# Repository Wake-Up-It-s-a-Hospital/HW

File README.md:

# Hardware

##### 환자 추종 스마트 링거 폴대의 PCB 및 HW 설계를 담당하는 레포지토리입니다.

_구동부, 손잡이부, 스마트 기능부에 해당하는 PCB 설계 및 회로도와 각각의 부분에 해당하는 HW 설계 및 3D modeling 등을 설계하였습니다._

본 레포지토리는 **2025년 한국공학대학교 종합설계 (캡스톤디자인) 프로젝트**와 **한이음 프로젝트**의 지원을 받아 개발되고 있습니다.

---
### ✅ 현재까지 완성한 Hardware

#### :diamond_shape_with_a_dot_inside: 1. 구동부 부분의 프로파일 및 아크릴 설계 도면

- 정육각형 구동부 상자의 모서리 역할인 프로파일 도면

- 정육각형 구동부 상자의 면 역할인 아크릴 설계 도면
  - 각종 PCB, 소자, 배터리, 폴대 장착에 맞추어 타공

#### :diamond_shape_with_a_dot_inside: 2.  PCB 설계 도면

- 구동부, 손잡이부, 스마트 기능부
 
- 각각 KiCAD를 사용해서 제작
  - 별칭
    - 구동부 : 1층
    - 손잡이부 : 2층
    - 카메라부 : 3층
    - 스마트 기능부 : 4층
    - 스마트 웨어러블 기기 : 시계부
-  2층* 을 제외한 모든 PCB 는 KiCAD 버전 9.0으로 작성됨.
  
-  2층은 KiCAD 8.0 버전으로 작성됨.

- connector는 모두 molex 5264(수), 5267(암)을 사용함.
- 전원 connector는 5557(수), 5566(암)을 사용함.

#### :diamond_shape_with_a_dot_inside: 3. 3D Modeling
- STM32로부터 수신한 데이터 패킷(lost 상황, 자동/수동 모드)을 AWS 서버로 전송

- NodeRed연동된 스마트 웨어러블 기기와 실시간으로 통신하여 경고 알림 제공

#### :diamond_shape_with_a_dot_inside: 4. 자동 / 수동 모드 전환 기능
- 링거 폴대 하부의 버튼 입력을 통해 자동 ↔ 수동 모드 전환 가능

---
## Data Flow

```mermaid
sequenceDiagram
    participant ESP32_LEFT as ESP32 (HUSKY_LEFT)
    participant STM32
    participant ESP32_RIGHT as ESP32 (HUSKY_RIGHT)

    ESP32_LEFT->>STM32: θ (조향각), currentMode (자동/수동)
    STM32->>ESP32_RIGHT: SoC (State of Charge)
    STM32->>ESP32_LEFT: lost 상태, SoC (State of Charge)

```

## 📁 주요 버전 디렉토리 구조

```
Patient-Recognition/
├── latest version/
|  ├──HUSKY_LEFT_AWS_V1_0       #ESP32 LEFT 
|  ├──HUSKY_RIGHT_WIFI_V1_0     #ESP32 RIGHT
├── test version/
|  ├──remote_control0           #이전 버전 원격 조정
|  ├──remote_control1           #최신 버전 원격 조정
|  ├──remote_master             #STM32 측 구동부
├── previous version/
|  ├──HUSKY_SERVO_V2_0          # 이전 버전 (서보모터 사용 허스키 1개)
|  ├──HUSKY_SErVO_V3_0
```

---

## 설치 및 실행 방법

### 1. HUSKYLENS 펌웨어
1) Arduino IDE 설치
2) HUSKYLENS header file 설치
[HUSKYLENS 공식 문서](https://wiki.dfrobot.com/HUSKYLENS_V1.0_SKU_SEN0305_SEN0336#target_6)

**헤더 파일 오류시**

HuskyLensProtocolCore.C에서

    uint8_t* husky_lens_protocol_write_begin()
    {
        return &send_buffer;
    }

에서 return 값 변경(ESP32와의 호환성 문제)

    uint8_t* husky_lens_protocol_write_begin()
    {
        return send_buffer;
    }

3) `latest version` 폴더 열어 LEFT, RIGHT 선택
4) 해당 코드에 맞는 좌우 HUSKYLENS 연결
5) 기본 HW 연결 세팅 확인 및 펌웨어 업로드

> :electric_plug: 기본 HW 세팅 회로도

### 2. HUSKYLENS HW 장착
 1) HW Repository Camera Cover file 열기
 2) HW Repository Camera Clamp file 열기
 3) HW Repository 2ndfloor_pole_bracket 열기
 4) HW Repository 2ndfloor_pole_bracket_RIGHT 열기
 5) 3D 프린터로 해당 Cover 인쇄 (2EA)
 6) 3D 프린터로 해당 Clamp 인쇄 (1EA)
 7) 3D 프린터로 해당 bracket, brackeet_RIGHT 인쇄 (각 1EA)
 8) 좌우 구분하여 LEFT, RIGHT HUSKYLENS 장착

 ### 3. STM32와의 통신선 연결 (UART)
 1) STM32와의 UART (TX, RX) 연결
 2) STM32와는 통신선 교차 연결

> :electric_plug: 기본 통신선 세팅 회로도

## :iphone: 주요 기능

### 환자 인식
 - 허스키렌즈를 통한 환자 인식
 - ID 별 인식 구별을 통한 다른 환자의 환자복 인식 방지 기능
 - 허스키렌즈 2개를 통한 조향각 매핑

 ### 데이터 통신
 - STM32와의 주요 factor 통신 (UART)
 - 스마트 웨어러블 기기와의 통신 (AWS NodeRed)

 ## :pushpin:  TODO (예정 기능)

 - [x] pull-up 저항 PCB 업데이트
 - [x] beacon 을 활용한 폴대 사용자의 위치 추정 기술
 - [x] 왼쪽 허스키 교체 (부품)
 - [x] ???

---
 ## 🤝 기여하기

1. 이 저장소를 포크합니다
2. 새로운 기능 브랜치를 생성합니다 (`git checkout -b feature/AmazingFeature`)
3. 변경사항을 커밋합니다 (`git commit -m 'Add some AmazingFeature'`)
4. 브랜치에 푸시합니다 (`git push origin feature/AmazingFeature`)
5. Pull Request를 생성합니다

---

## 📝 라이선스

이 프로젝트는 [MIT License](LICENSE)를 따릅니다. 자유롭게 사용, 수정, 배포하셔도 좋습니다.

---

## 📬 연락처

- ✉️ dy061932@tukorea.ac.kr  (학교)
- ✉️ dy353020@naver.com      (개인)

---

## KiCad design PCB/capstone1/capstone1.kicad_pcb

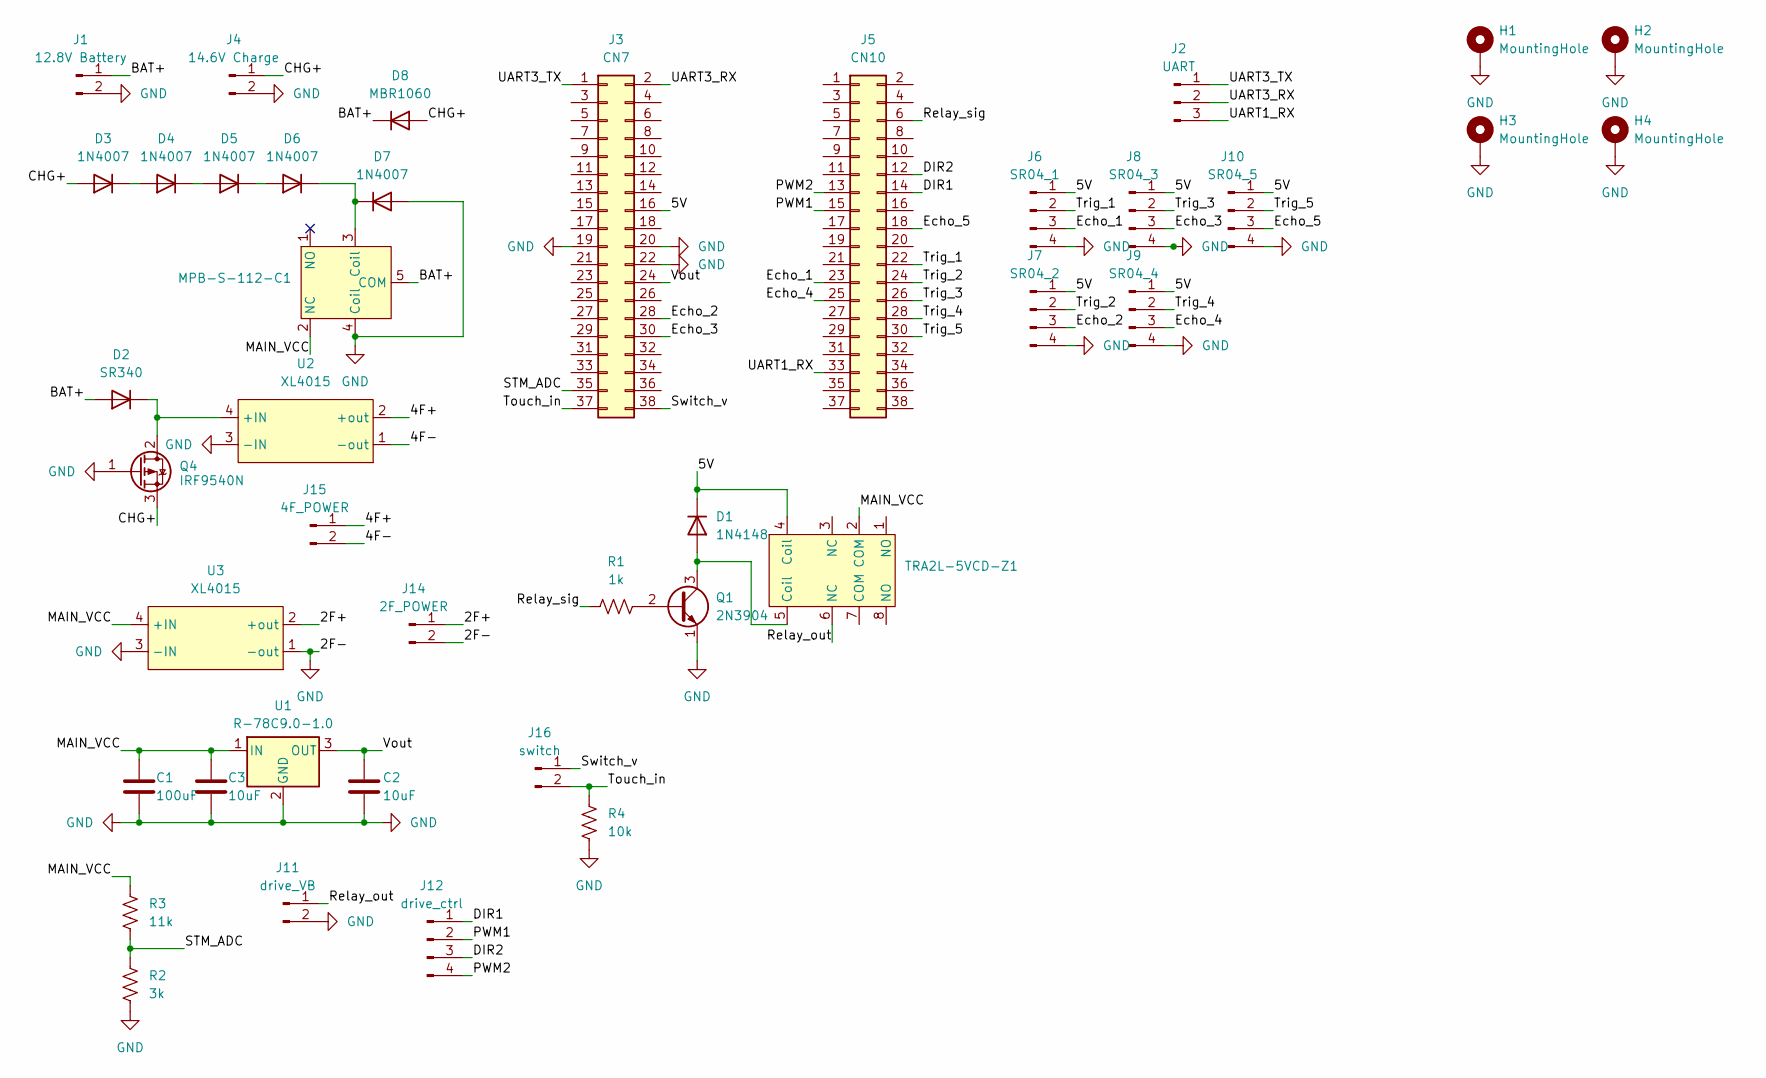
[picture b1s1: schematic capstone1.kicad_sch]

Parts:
C1: 100uF; CP_Elec_6.3x5.3
C2, C3: 10uF; C_1206_3216Metric
D1: 1N4148; D_DO-35_SOD27_P7.62mm_Horizontal
D2: SR340; D_DO-41_SOD81_P10.16mm_Horizontal
D3, D4, D5, D6, D7: 1N4007; D_DO-41_SOD81_P10.16mm_Horizontal
D8: MBR1060; TO-220-2_Vertical
H1, H2, H3, H4: MountingHole; MountingHole_2.5mm_Pad
J1: 12.8V Battery; Molex_Mini-Fit_Jr_5566-02A_2x01_P4.20mm_Vertical
J2: UART; Molex_SPOX_5267-03A_1x03_P2.50mm_Vertical
J3: CN7; PinSocket_2x19_P2.54mm_Vertical
J4: 14.6V Charge; Molex_Mini-Fit_Jr_5566-02A_2x01_P4.20mm_Vertical
J5: CN10; PinSocket_2x19_P2.54mm_Vertical
J6: SR04_1; Molex_SPOX_5267-04A_1x04_P2.50mm_Vertical
J7: SR04_2; Molex_SPOX_5267-04A_1x04_P2.50mm_Vertical
J8: SR04_3; Molex_SPOX_5267-04A_1x04_P2.50mm_Vertical
J9: SR04_4; Molex_SPOX_5267-04A_1x04_P2.50mm_Vertical
J10: SR04_5; Molex_SPOX_5267-04A_1x04_P2.50mm_Vertical
J11: drive_VB; Molex_Mini-Fit_Jr_5566-02A_2x01_P4.20mm_Vertical
J12: drive_ctrl; Molex_SPOX_5267-04A_1x04_P2.50mm_Vertical
J14: 2F_POWER; Molex_Mini-Fit_Jr_5566-02A_2x01_P4.20mm_Vertical
J15: 4F_POWER; Molex_Mini-Fit_Jr_5566-02A_2x01_P4.20mm_Vertical
J16: switch; Molex_Mini-Fit_Jr_5566-02A_2x01_P4.20mm_Vertical
MPB-S-112-C1: MPB-S-112-C
Q1: 2N3904; TO-92_Inline
Q4: IRF9540N; TO-220-3_Vertical
R1: 1k; R_1206_3216Metric
R2: 3k; R_1206_3216Metric
R3: 11k; R_1206_3216Metric
R4: 10k; R_1206_3216Metric
TRA2L-5VCD-Z1: TRA2L-5VCD-Z
U1: R-78C9.0-1.0; Converter_DCDC_RECOM_R-78E-0.5_THT
U2, U3: XL4015

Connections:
/2F+: J14.1, U3.2 (+out)
/4F+: J15.1, U2.2 (+out)
/4F-: J15.2, U2.1 (-out)
/5V: D1.1 (K), J3.16, J6.1, J7.1, J8.1, J9.1, J10.1, TRA2L-5VCD-Z1.4 (Coil)
/BAT+: D2.2 (A), D8.1 (K), J1.1, MPB-S-112-C1.5 (COM)
/CHG+: D3.2 (A), D8.2 (A), J4.1, Q4.3 (S)
/DIR1: J5.14, J12.1
/DIR2: J5.12, J12.3
/Echo_1: J5.23, J6.3
/Echo_2: J3.28, J7.3
/Echo_3: J3.30, J8.3
/Echo_4: J5.25, J9.3
/Echo_5: J5.18, J10.3
/MAIN_VCC: C1.1, C3.1, MPB-S-112-C1.2 (NC), R3.1, TRA2L-5VCD-Z1.2 (COM), U1.1 (IN), U3.4 (+IN)
/PWM1: J5.15, J12.2
/PWM2: J5.13, J12.4
/Relay_out: J11.1, TRA2L-5VCD-Z1.6 (NC)
/Relay_sig: J5.6, R1.1
/STM_ADC: J3.35, R2.1, R3.2
/Switch_v: J3.38, J16.1
/Touch_in: J3.37, J16.2, R4.1
/Trig_1: J5.22, J6.2
/Trig_2: J5.24, J7.2
/Trig_3: J5.26, J8.2
/Trig_4: J5.28, J9.2
/Trig_5: J5.30, J10.2
/UART1_RX: J2.3, J5.33
/UART3_RX: J2.2, J3.2
/UART3_TX: J2.1, J3.1
/Vout: C2.1, J3.24, U1.3 (OUT)
GND: C1.2, C2.2, C3.2, D7.2 (A), H1.1, H2.1, H3.1, H4.1, J1.2, J3.19, J3.20, J3.22, J4.2, J6.4, J7.4, J8.4, J9.4, J10.4, J11.2, J14.2, MPB-S-112-C1.4 (Coil), Q1.1 (E), Q4.1 (G), R2.2, R4.2, U1.2 (GND), U2.3 (-IN), U3.1 (-out), U3.3 (-IN)
unnamed: D1.2 (A), Q1.3 (C), TRA2L-5VCD-Z1.5 (Coil)
unnamed: D2.1 (K), Q4.2 (D), U2.4 (+IN)
unnamed: D3.1 (K), D4.2 (A)
unnamed: D4.1 (K), D5.2 (A)
unnamed: D5.1 (K), D6.2 (A)
unnamed: D6.1 (K), D7.1 (K), MPB-S-112-C1.3 (Coil)
unnamed: Q1.2 (B), R1.2

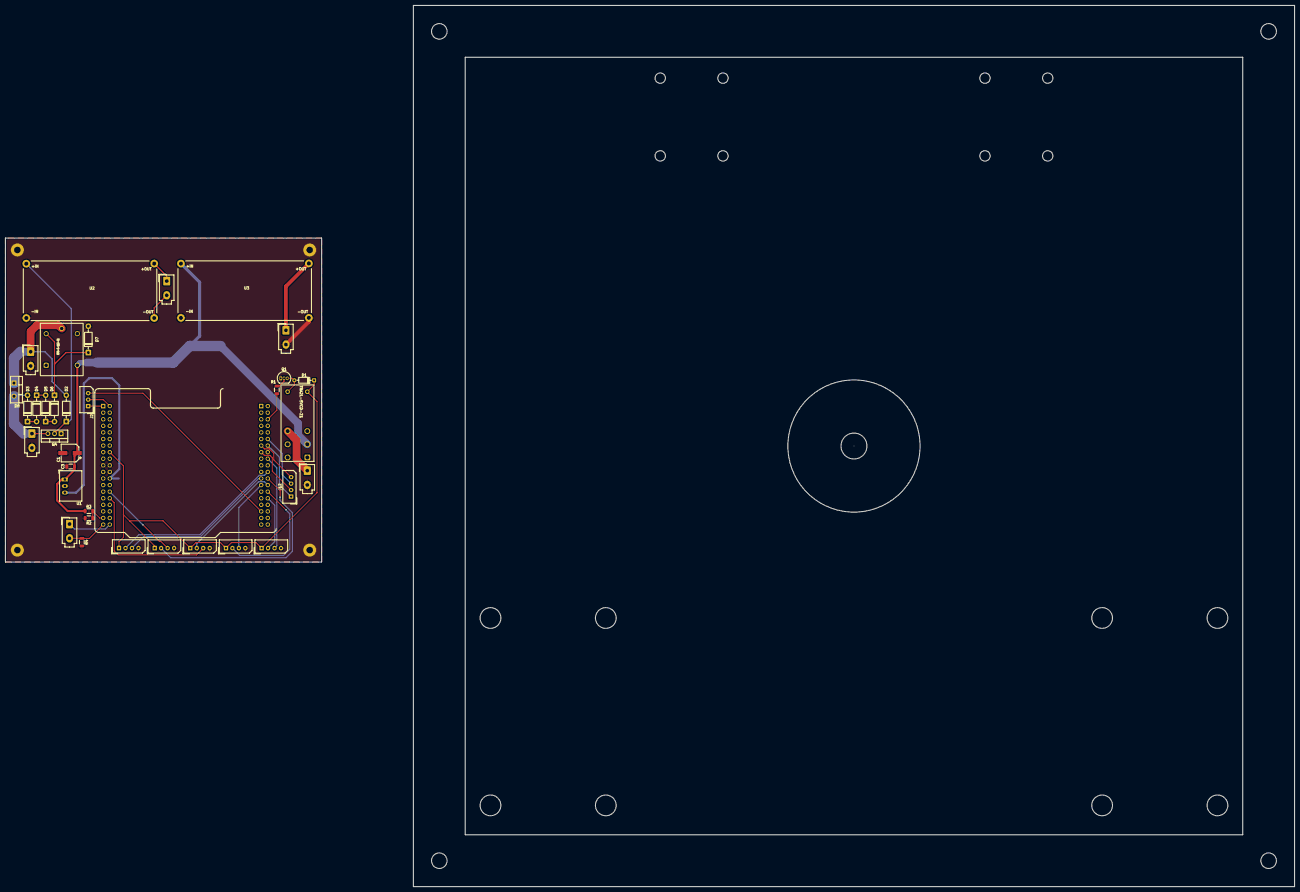
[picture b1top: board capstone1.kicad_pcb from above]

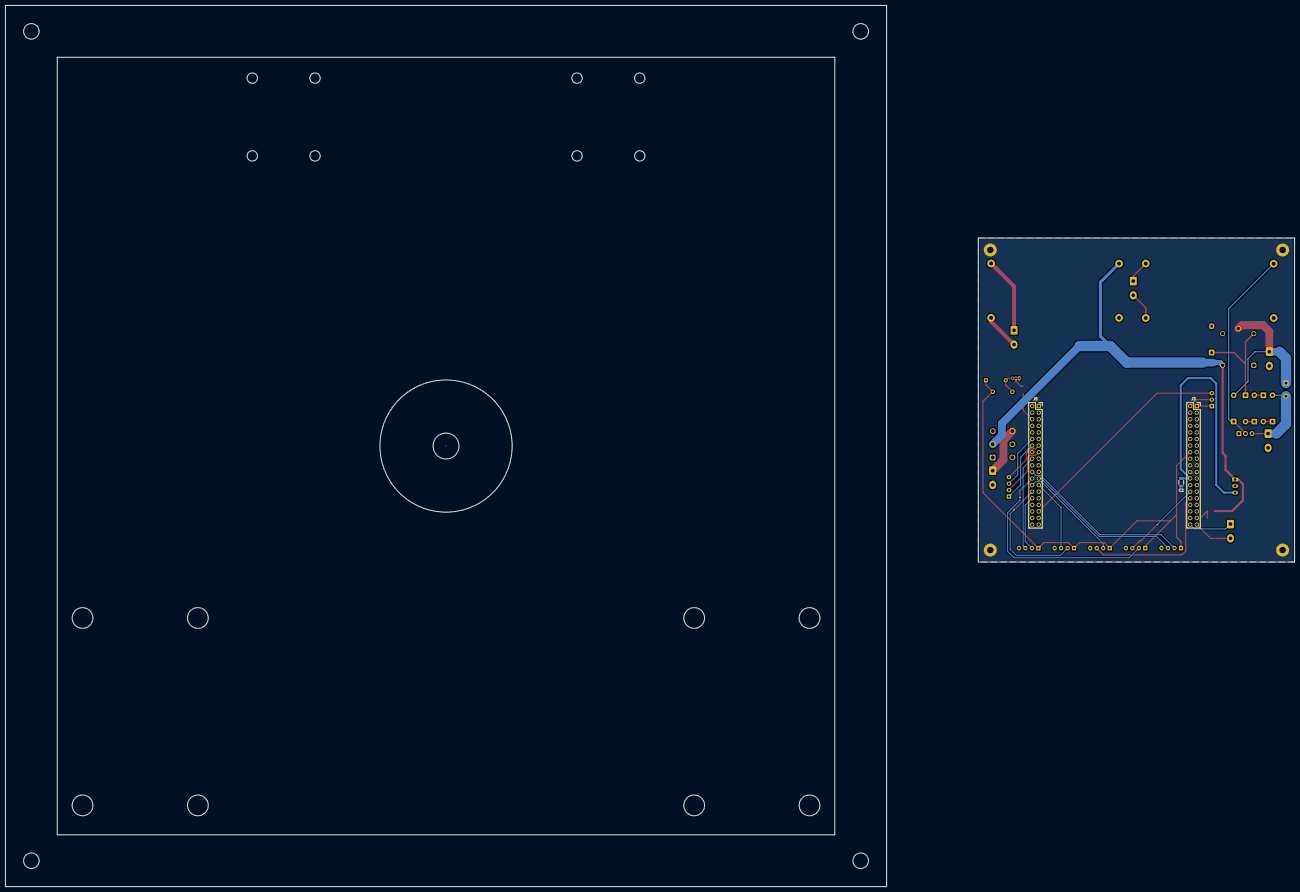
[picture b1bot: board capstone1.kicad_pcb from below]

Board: 2 copper layers, 122.0 x 125.0 mm, 41 parts (3 on the bottom side), 38 nets.

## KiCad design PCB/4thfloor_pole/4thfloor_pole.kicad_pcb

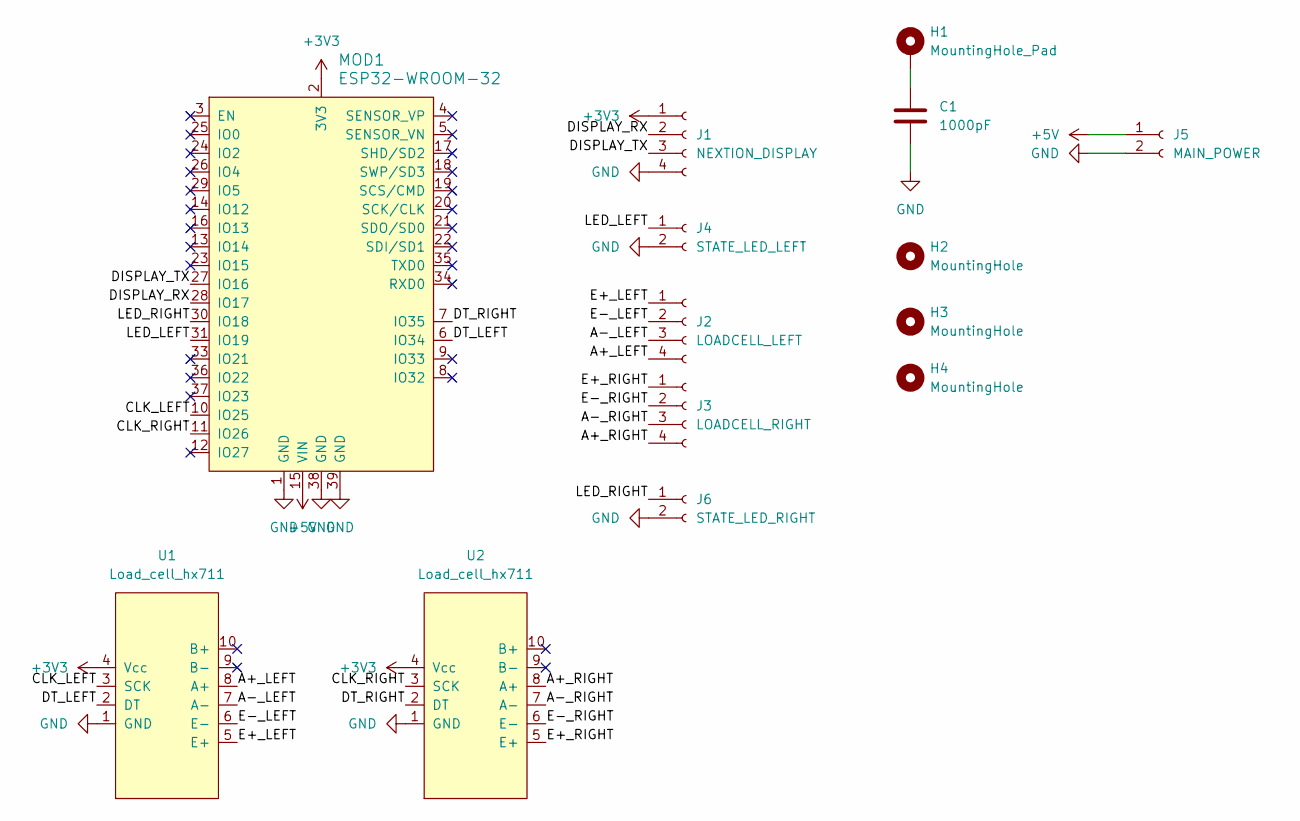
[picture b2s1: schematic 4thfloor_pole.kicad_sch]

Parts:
C1: 1000pF; C_Disc_D9.0mm_W2.5mm_P5.00mm
H1: MountingHole_Pad; MountingHole_3.5mm_Pad
H2, H3, H4: MountingHole; MountingHole_3.5mm_Pad
J1: NEXTION_DISPLAY; Molex_SPOX_5267-04A_1x04_P2.50mm_Vertical
J2: LOADCELL_LEFT; Molex_SPOX_5267-04A_1x04_P2.50mm_Vertical
J3: LOADCELL_RIGHT; Molex_SPOX_5267-04A_1x04_P2.50mm_Vertical
J4: STATE_LED_LEFT; Molex_SPOX_5267-02A_1x02_P2.50mm_Vertical
J5: MAIN_POWER; Molex_Mini-Fit_Jr_5566-02A_2x01_P4.20mm_Vertical
J6: STATE_LED_RIGHT; Molex_SPOX_5267-02A_1x02_P2.50mm_Vertical
MOD1: ESP32-WROOM-32; ESP32_new_modified; MPN ESP32-WROOM-32; Digi-Key_PN 1904-1010-1-ND
U1, U2: Load_cell_hx711; loadcell

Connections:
+3V3: J1.1, MOD1.2 (3V3), U1.4 (Vcc), U2.4 (Vcc)
+5V: J5.1, MOD1.15 (VIN)
/A+_LEFT: J2.4, U1.8 (A+)
/A+_RIGHT: J3.4, U2.8 (A+)
/A-_LEFT: J2.3, U1.7 (A-)
/A-_RIGHT: J3.3, U2.7 (A-)
/CLK_LEFT: MOD1.10 (IO25), U1.3 (SCK)
/CLK_RIGHT: MOD1.11 (IO26), U2.3 (SCK)
/DISPLAY_RX: J1.2, MOD1.28 (IO17)
/DISPLAY_TX: J1.3, MOD1.27 (IO16)
/DT_LEFT: MOD1.6 (IO34), U1.2 (DT)
/DT_RIGHT: MOD1.7 (IO35), U2.2 (DT)
/E+_LEFT: J2.1, U1.5 (E+)
/E+_RIGHT: J3.1, U2.5 (E+)
/E-_LEFT: J2.2, U1.6 (E-)
/E-_RIGHT: J3.2, U2.6 (E-)
/LED_LEFT: J4.1, MOD1.31 (IO19)
/LED_RIGHT: J6.1, MOD1.30 (IO18)
GND: C1.2, J1.4, J4.2, J5.2, J6.2, MOD1.1 (GND), MOD1.38 (GND), MOD1.39 (GND), U1.1 (GND), U2.1 (GND)
unnamed: C1.1, H1.1

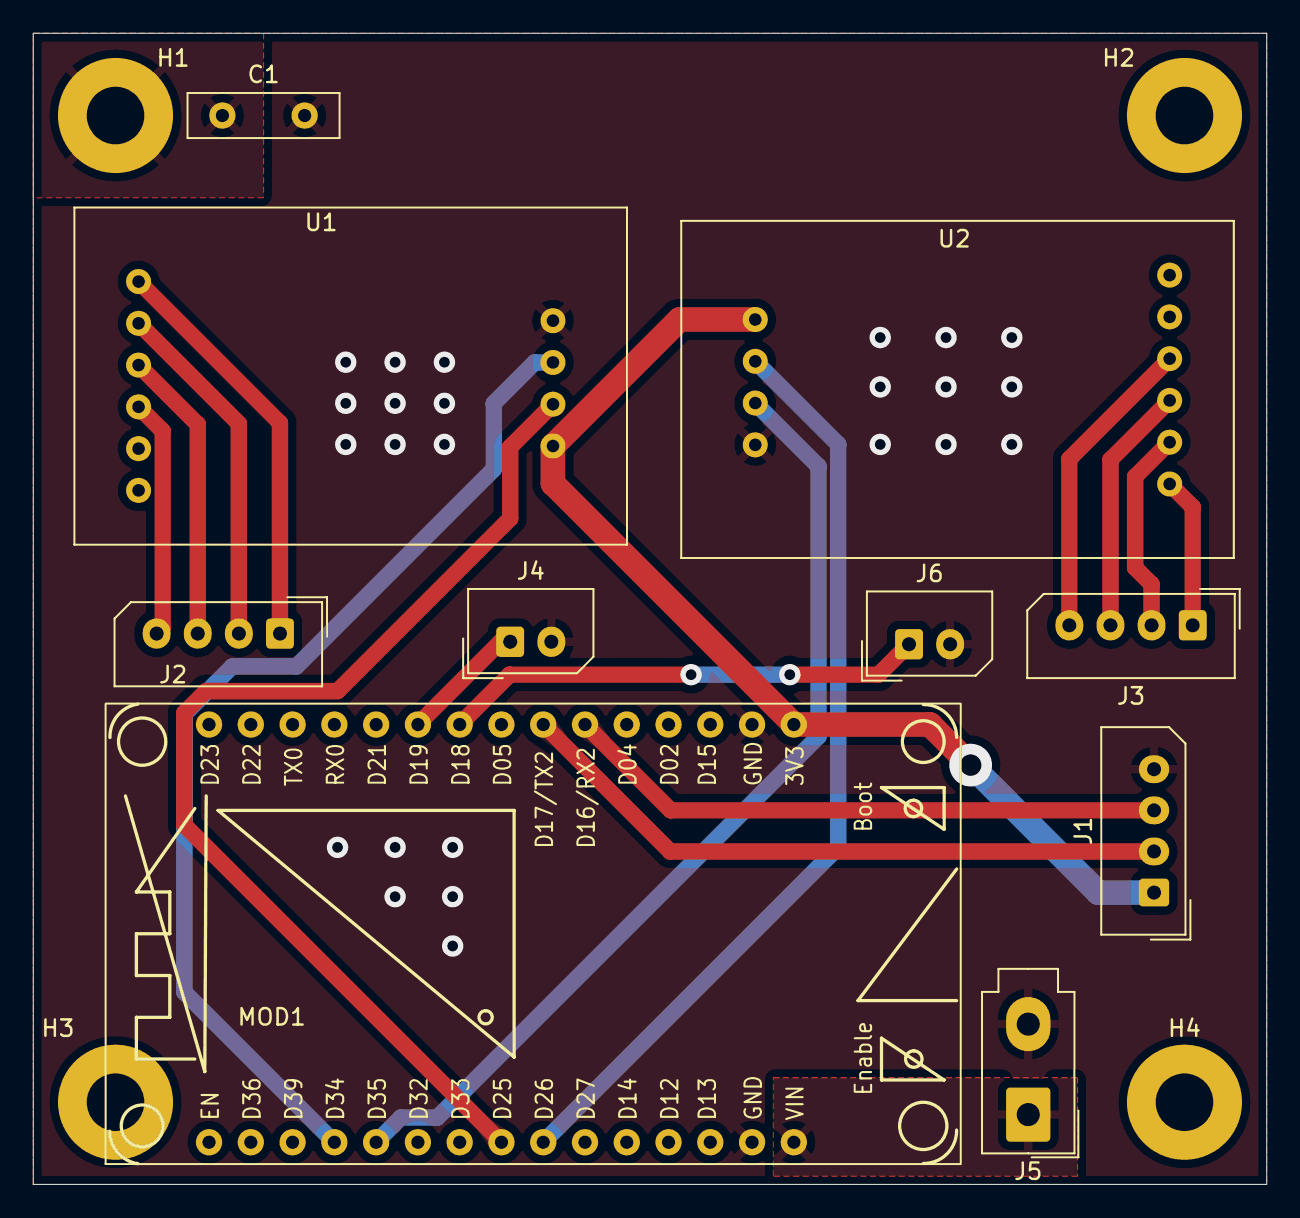
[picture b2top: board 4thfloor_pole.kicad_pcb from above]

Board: 2 copper layers, 75.0 x 70.0 mm, 14 parts (0 on the bottom side), 20 nets.

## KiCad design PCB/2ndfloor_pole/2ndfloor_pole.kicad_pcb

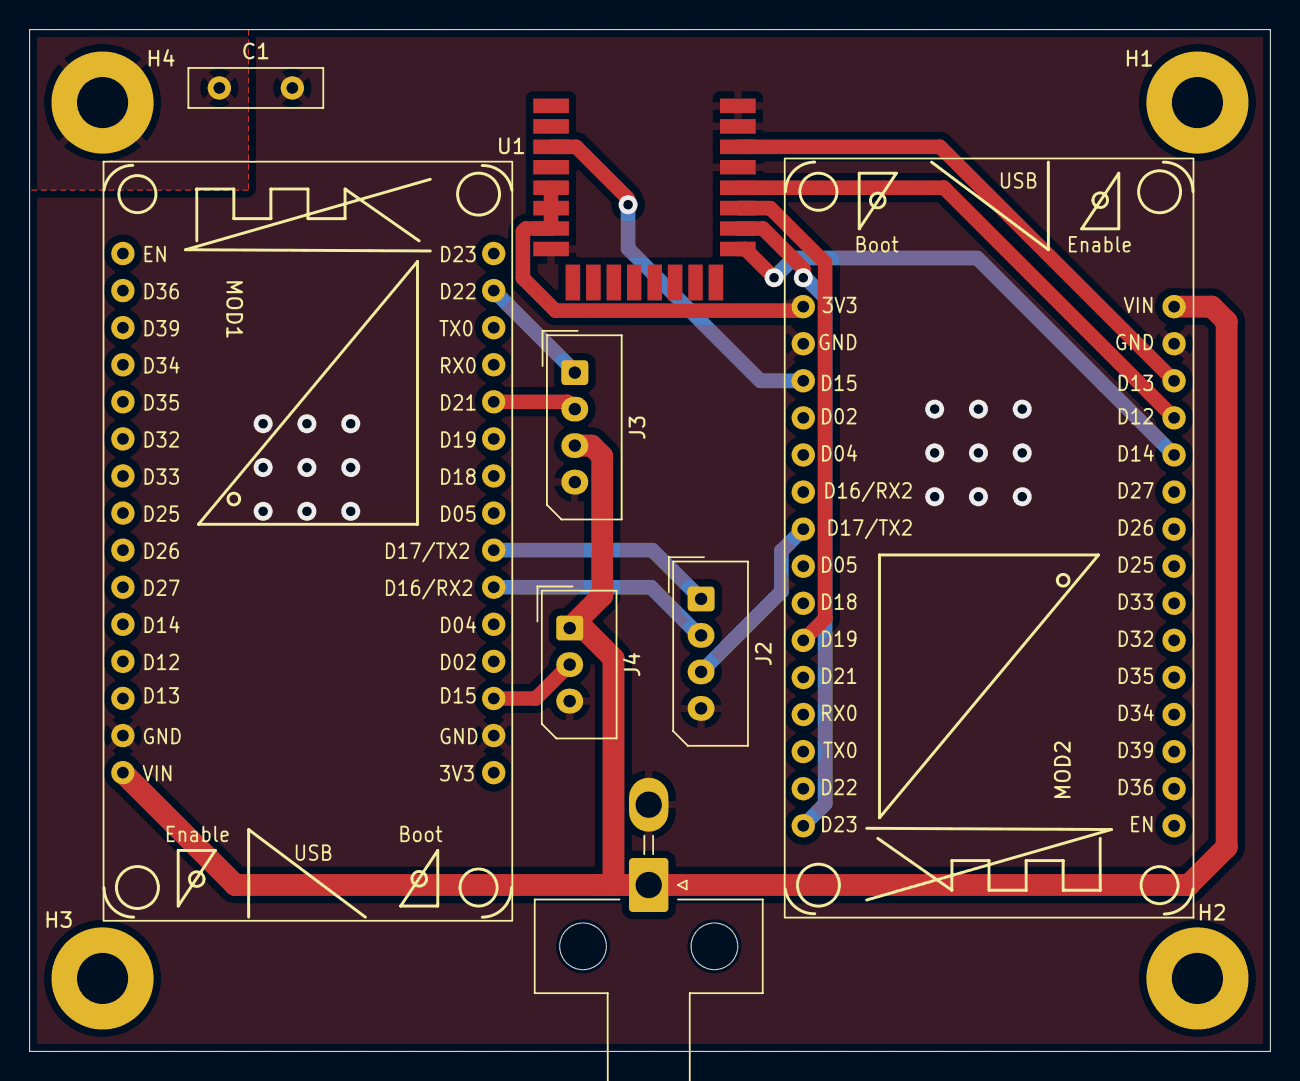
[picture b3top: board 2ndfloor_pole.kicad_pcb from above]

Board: 2 copper layers, 85.0 x 70.0 mm, 12 parts (0 on the bottom side), 16 nets.

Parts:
C1: 1000pF; C_Disc_D9.0mm_W2.5mm_P5.00mm
H1, H2, H3: MountingHole; MountingHole_3.5mm_Pad
H4: MountingHole_Pad; MountingHole_3.5mm_Pad
J1: MAIN_POWER; Molex_Mini-Fit_Jr_5569-02A1_2x01_P4.20mm_Horizontal
J2: STM32<->ESP32-HUSKYLENS; Molex_SPOX_5267-04A_1x04_P2.50mm_Vertical
J3: HUSYYLENS; Molex_SPOX_5267-04A_1x04_P2.50mm_Vertical
J4: Servo(MG-90S); Molex_SPOX_5267-03A_1x03_P2.50mm_Vertical
MOD1: ESP32 - HUSKYLENS; ESP32_new
MOD2: ESP-UWB; ESP32_new
U1: DWM1000; XCVR_DWM1000

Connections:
+3.3V: MOD2.2 (3V3), U1.5 (VDDAON), U1.6 (VDD3V3@1), U1.7 (VDD3V3@2)
+5V: J1.1, J3.3, J4.1, MOD1.15 (VIN), MOD2.15 (VIN)
/CLK: MOD2.14 (IO12), U1.20 (SPICLK)
/CS: MOD2.13 (IO14), U1.17 (SPICSN)
/HUSKY_RX: J2.2, MOD1.27 (IO16)
/HUSKY_TX: J2.1, MOD1.28 (IO17)
/IRQ: MOD2.16 (IO13), U1.22 (IRQ/GPIO8)
/MISO: MOD2.31 (IO19), U1.19 (SPIMISO)
/MOSI: MOD2.37 (IO23), U1.18 (SPIMOSI)
/PWM_PIN: J4.2, MOD1.23 (IO15)
/RST: MOD2.23 (IO15), U1.3 (RSTN)
/SCL: J3.1, MOD1.36 (IO22)
/SDA: J3.2, MOD1.33 (IO21)
/UWB_TX: J2.3, MOD2.28 (IO17)
GND: C1.2, J1.2, J2.4, J3.4, J4.3, MOD1.1 (GND), MOD2.1 (GND), U1.8 (VSS@1), U1.21 (VSS@3), U1.23 (VSS@4), U1.24 (VSS@5)
unnamed: C1.1, H4.1

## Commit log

2025-05-25 아크릴 및 프로파일 설계도면&파일
2025-08-07 HW 부 최종 업데이트
    파일 최신화
2025-08-13 초기 업데이트

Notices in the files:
README.md:
License: MIT
